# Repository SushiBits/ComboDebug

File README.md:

# ComboDebug ARM JTAG Adapter

ComboDebug is a companion adapter for [DAP42][DAP42] debug probe, as well as
standard ARM debuggers with 2.54mm 20-pin interface like [J-Link][JLINK] and
[ST-Link][SLINK].

## Introduction

DAP42 is a CMSIS-DAP compatible USB JTAG debug adapter for ARM Cortex-A and
Cortex-M processors, based on the [STM32F042K6][42K] microcontroller.

This adapter provides a 1.27mm 10-pin modified Cortex Debug Connector with two
of the original ground lines replaced with a serial port.

The serial port can be handled through the DAP42 host interface, or through an
onboard USB to Serial adapter.

It also provides an external target reset button, and an offline programming
trigger button for [DAP42][DAP42]

## License and contact

This is open source hardware under [3-clause BSD license][3BSDL].

[JLINK]: https://www.segger.com/products/debug-probes/j-link/
[SLINK]: http://www.st.com/en/development-tools/st-link-v2.html
[42K]:   http://www.st.com/en/microcontrollers/stm32f042k6.html
[DAP42]: https://github.com/SushiBits/DAP42
[3BSDL]: LICENSE.md

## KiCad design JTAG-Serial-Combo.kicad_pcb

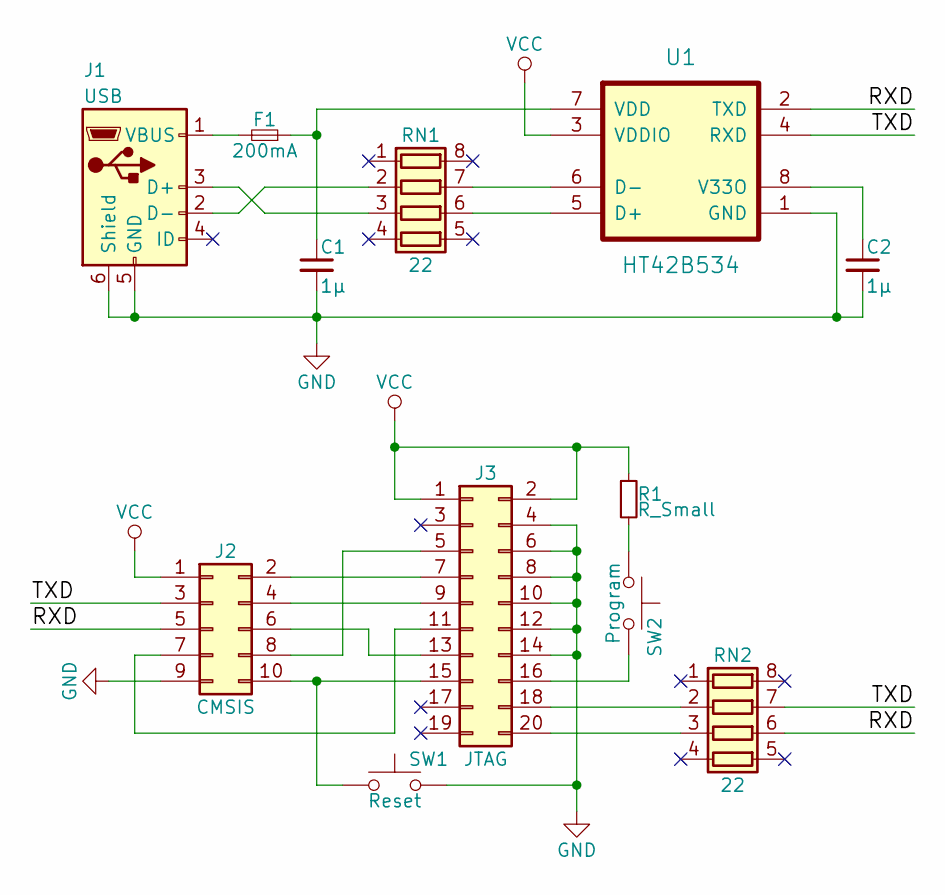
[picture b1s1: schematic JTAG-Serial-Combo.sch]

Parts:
C1, C2: 1µ; C_0603_HandSoldering
F1: 200mA; R_0805_HandSoldering
J1: USB; USB_Micro-B
J2: CMSIS; Pin_Header_Straight_2x05_Pitch1.27mm_SMD
J3: JTAG; Socket_Strip_Straight_2x10_Pitch2.54mm
R1: R_Small; R_0603_HandSoldering
RN1, RN2: 22; R_Array_Concave_4x0603
SW1: Reset; SW_SPST_FSMSM
SW2: Program; SW_SPST_FSMSM
U1: HT42B534; SOIC-8_3.9x4.9mm_Pitch1.27mm

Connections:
/RXD: J2.5, RN2.6 (R3.2), U1.2 (TXD)
/TXD: J2.3, RN2.7 (R2.2), U1.4 (RXD)
GND: C1.2, C2.2, J1.5 (GND), J1.6 (Shield), J2.9, J3.4, J3.6, J3.8, J3.10, J3.12, J3.14, SW1.2, U1.1 (GND)
unnamed: C1.1, F1.1, U1.7 (VDD)
unnamed: C2.1, U1.8 (V33O)
unnamed: F1.2, J1.1 (VBUS)
unnamed: J1.2 (D-), RN1.2 (R2.1)
unnamed: J1.3 (D+), RN1.3 (R3.1)
unnamed: J2.2, J3.7
unnamed: J2.4, J3.9
unnamed: J2.6, J3.13
unnamed: J2.7, J3.11
unnamed: J2.8, J3.5
unnamed: J2.10, J3.15, SW1.1
unnamed: J3.16, SW2.2
unnamed: J3.18, RN2.2 (R2.1)
unnamed: J3.20, RN2.3 (R3.1)
unnamed: R1.2, SW2.1
unnamed: RN1.6 (R3.2), U1.5 (D+)
unnamed: RN1.7 (R2.2), U1.6 (D-)
VCC: J2.1, J3.1, J3.2, R1.1, U1.3 (VDDIO)

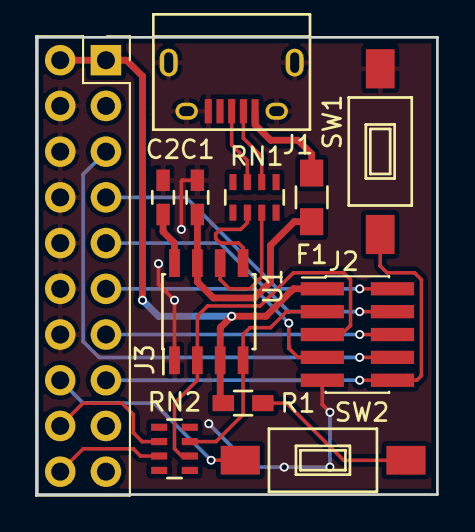
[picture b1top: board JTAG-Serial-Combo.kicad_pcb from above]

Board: 2 copper layers, 22.2 x 25.4 mm, 12 parts (0 on the bottom side), 21 nets.

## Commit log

2018-02-26 Including project files
2018-02-26 Improved README
2018-02-26 Added a section to README
